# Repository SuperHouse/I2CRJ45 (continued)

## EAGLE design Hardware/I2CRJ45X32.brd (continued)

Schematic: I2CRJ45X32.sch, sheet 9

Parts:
C10: 10uF; C0805
IC7: MCP23017SO; SO28W
J13: I2C Addr 6; 2X03-P
RN55, RN56, RN57, RN58: 1K; CAY16
RN59, RN60, RN61, RN62, RN63: 10K; CAY16

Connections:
4A1: RN55.5 (2), RN62.4 (1); also elsewhere on the board
4A2: RN55.6 (2), RN62.3 (1); also elsewhere on the board
4A3: RN55.7 (2), RN62.2 (1); also elsewhere on the board
4A6: RN55.8 (2), RN62.1; also elsewhere on the board
4B1: RN57.5 (2), RN60.4 (1); also elsewhere on the board
4B2: RN57.6 (2), RN60.3 (1); also elsewhere on the board
4B3: RN57.7 (2), RN60.2 (1); also elsewhere on the board
4B6: RN57.8 (2), RN60.1; also elsewhere on the board
4E1: RN56.5 (2), RN61.4 (1); also elsewhere on the board
4E2: RN56.6 (2), RN61.3 (1); also elsewhere on the board
4E3: RN56.7 (2), RN61.2 (1); also elsewhere on the board
4E6: RN56.8 (2), RN61.1; also elsewhere on the board
4F1: RN58.5 (2), RN59.4 (1); also elsewhere on the board
4F2: RN58.6 (2), RN59.3 (1); also elsewhere on the board
4F3: RN58.7 (2), RN59.2 (1); also elsewhere on the board
4F6: RN58.8 (2), RN59.1; also elsewhere on the board
!INT: IC7.20 (INTA); also elsewhere on the board
!RESET: IC7.18 (!RESET); also elsewhere on the board
GND: C10.2, IC7.10 (VSS), RN63.1, RN63.2 (1), RN63.3 (1), RN63.4 (1); also elsewhere on the board
GPA0-7: IC7.21 (GPA0), RN55.4 (1)
GPA1-7: IC7.22 (GPA1), RN55.3 (1)
GPA2-7: IC7.23 (GPA2), RN55.2 (1)
GPA3-7: IC7.24 (GPA3), RN55.1
GPA4-7: IC7.25 (GPA4), RN56.4 (1)
GPA5-7: IC7.26 (GPA5), RN56.3 (1)
GPA6-7: IC7.27 (GPA6), RN56.2 (1)
GPA7-7: IC7.28 (GPA7), RN56.1
GPB0-7: IC7.1 (GPB0), RN57.4 (1)
GPB1-7: IC7.2 (GPB1), RN57.3 (1)
GPB2-7: IC7.3 (GPB2), RN57.2 (1)
GPB3-7: IC7.4 (GPB3), RN57.1
GPB4-7: IC7.5 (GPB4), RN58.4 (1)
GPB5-7: IC7.6 (GPB5), RN58.3 (1)
GPB6-7: IC7.7 (GPB6), RN58.2 (1)
GPB7-7: IC7.8 (GPB7), RN58.1
unnamed: IC7.17 (A2), J13.6, RN63.8 (2)
unnamed: IC7.15 (A0), J13.2, RN63.6 (2)
unnamed: IC7.16 (A1), J13.4, RN63.7 (2)
SCL: IC7.12 (SCL); also elsewhere on the board
SDA: IC7.13 (SDA); also elsewhere on the board
VCC: C10.1, IC7.9 (VDD), J13.1, J13.3, J13.5, RN59.5 (2), RN59.6 (2), RN59.7 (2), RN59.8 (2), RN60.5 (2), RN60.6 (2), RN60.7 (2), RN60.8 (2), RN61.5 (2), RN61.6 (2), RN61.7 (2), RN61.8 (2), RN62.5 (2), RN62.6 (2), RN62.7 (2), RN62.8 (2); also elsewhere on the board

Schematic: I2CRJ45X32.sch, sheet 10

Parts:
C11: 10uF; C0805
IC8: MCP23017SO; SO28W
J14: I2C Addr 6; 2X03-P
RN64, RN65, RN66, RN67: 1K; CAY16
RN68, RN69, RN70, RN71, RN72: 10K; CAY16

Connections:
4C1: RN64.5 (2), RN71.4 (1); also elsewhere on the board
4C2: RN64.6 (2), RN71.3 (1); also elsewhere on the board
4C3: RN64.7 (2), RN71.2 (1); also elsewhere on the board
4C6: RN64.8 (2), RN71.1; also elsewhere on the board
4D1: RN66.5 (2), RN69.4 (1); also elsewhere on the board
4D2: RN66.6 (2), RN69.3 (1); also elsewhere on the board
4D3: RN66.7 (2), RN69.2 (1); also elsewhere on the board
4D6: RN66.8 (2), RN69.1; also elsewhere on the board
4G1: RN65.5 (2), RN70.4 (1); also elsewhere on the board
4G2: RN65.6 (2), RN70.3 (1); also elsewhere on the board
4G3: RN65.7 (2), RN70.2 (1); also elsewhere on the board
4G6: RN65.8 (2), RN70.1; also elsewhere on the board
4H1: RN67.5 (2), RN68.4 (1); also elsewhere on the board
4H2: RN67.6 (2), RN68.3 (1); also elsewhere on the board
4H3: RN67.7 (2), RN68.2 (1); also elsewhere on the board
4H6: RN67.8 (2), RN68.1; also elsewhere on the board
!INT: IC8.20 (INTA); also elsewhere on the board
!RESET: IC8.18 (!RESET); also elsewhere on the board
GND: C11.2, IC8.10 (VSS), RN72.1, RN72.2 (1), RN72.3 (1), RN72.4 (1); also elsewhere on the board
GPA0-8: IC8.21 (GPA0), RN64.4 (1)
GPA1-8: IC8.22 (GPA1), RN64.3 (1)
GPA2-8: IC8.23 (GPA2), RN64.2 (1)
GPA3-8: IC8.24 (GPA3), RN64.1
GPA4-8: IC8.25 (GPA4), RN65.4 (1)
GPA5-8: IC8.26 (GPA5), RN65.3 (1)
GPA6-8: IC8.27 (GPA6), RN65.2 (1)
GPA7-8: IC8.28 (GPA7), RN65.1
GPB0-8: IC8.1 (GPB0), RN66.4 (1)
GPB1-8: IC8.2 (GPB1), RN66.3 (1)
GPB2-8: IC8.3 (GPB2), RN66.2 (1)
GPB3-8: IC8.4 (GPB3), RN66.1
GPB4-8: IC8.5 (GPB4), RN67.4 (1)
GPB5-8: IC8.6 (GPB5), RN67.3 (1)
GPB6-8: IC8.7 (GPB6), RN67.2 (1)
GPB7-8: IC8.8 (GPB7), RN67.1
unnamed: IC8.17 (A2), J14.6, RN72.8 (2)
unnamed: IC8.15 (A0), J14.2, RN72.6 (2)
unnamed: IC8.16 (A1), J14.4, RN72.7 (2)
SCL: IC8.12 (SCL); also elsewhere on the board
SDA: IC8.13 (SDA); also elsewhere on the board
VCC: C11.1, IC8.9 (VDD), J14.1, J14.3, J14.5, RN68.5 (2), RN68.6 (2), RN68.7 (2), RN68.8 (2), RN69.5 (2), RN69.6 (2), RN69.7 (2), RN69.8 (2), RN70.5 (2), RN70.6 (2), RN70.7 (2), RN70.8 (2), RN71.5 (2), RN71.6 (2), RN71.7 (2), RN71.8 (2); also elsewhere on the board

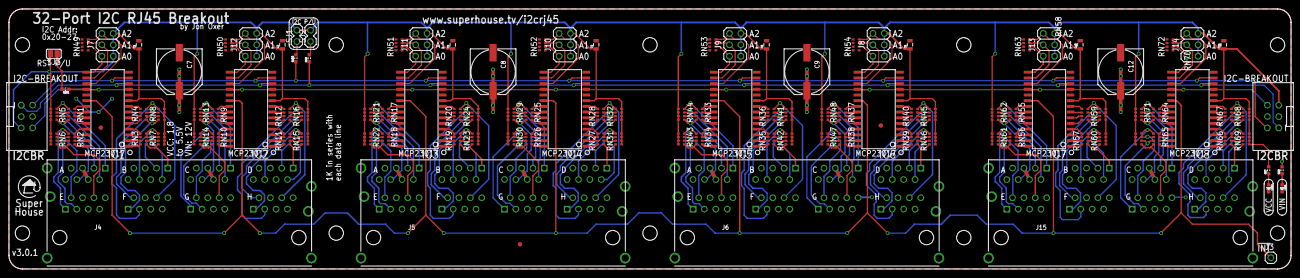
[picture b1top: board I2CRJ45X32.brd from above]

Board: 2 copper layers, 286.0 x 58.0 mm, 120 parts (0 on the bottom side), 292 nets.

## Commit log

2021-07-20 Separation of I2C breakouts from main LSC project.
2021-07-20 Removed LSC photo and description.
2021-07-20 Updated renders.
2021-07-30 Added 3D models of all board versions and header assembly jig.
2021-07-30 Added label to show pinout.
2021-07-31 Added mechanical drawings by Aaron Knox.
2021-09-05 Added 32-port version.
2021-09-10 Final tweaks and DRC for v3.0.1 release.
